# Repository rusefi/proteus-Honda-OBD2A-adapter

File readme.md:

https://github.com/rusefi/rusefi and https://github.com/mck1117/proteus

https://github.com/rusefi/rusefi/wiki/Vault-Of-Honda-OEM#obd-2

https://github.com/rusefi/rusefi/wiki/Honda-Civic-1996

https://github.com/rusefi/rusefi/wiki/Honda-Accord-1995

[Connector spreadsheet](https://docs.google.com/spreadsheets/d/1NOu2Atvwz7war0sTAcp2MZZhsYdLY6VmwkuC-S1-yEU)

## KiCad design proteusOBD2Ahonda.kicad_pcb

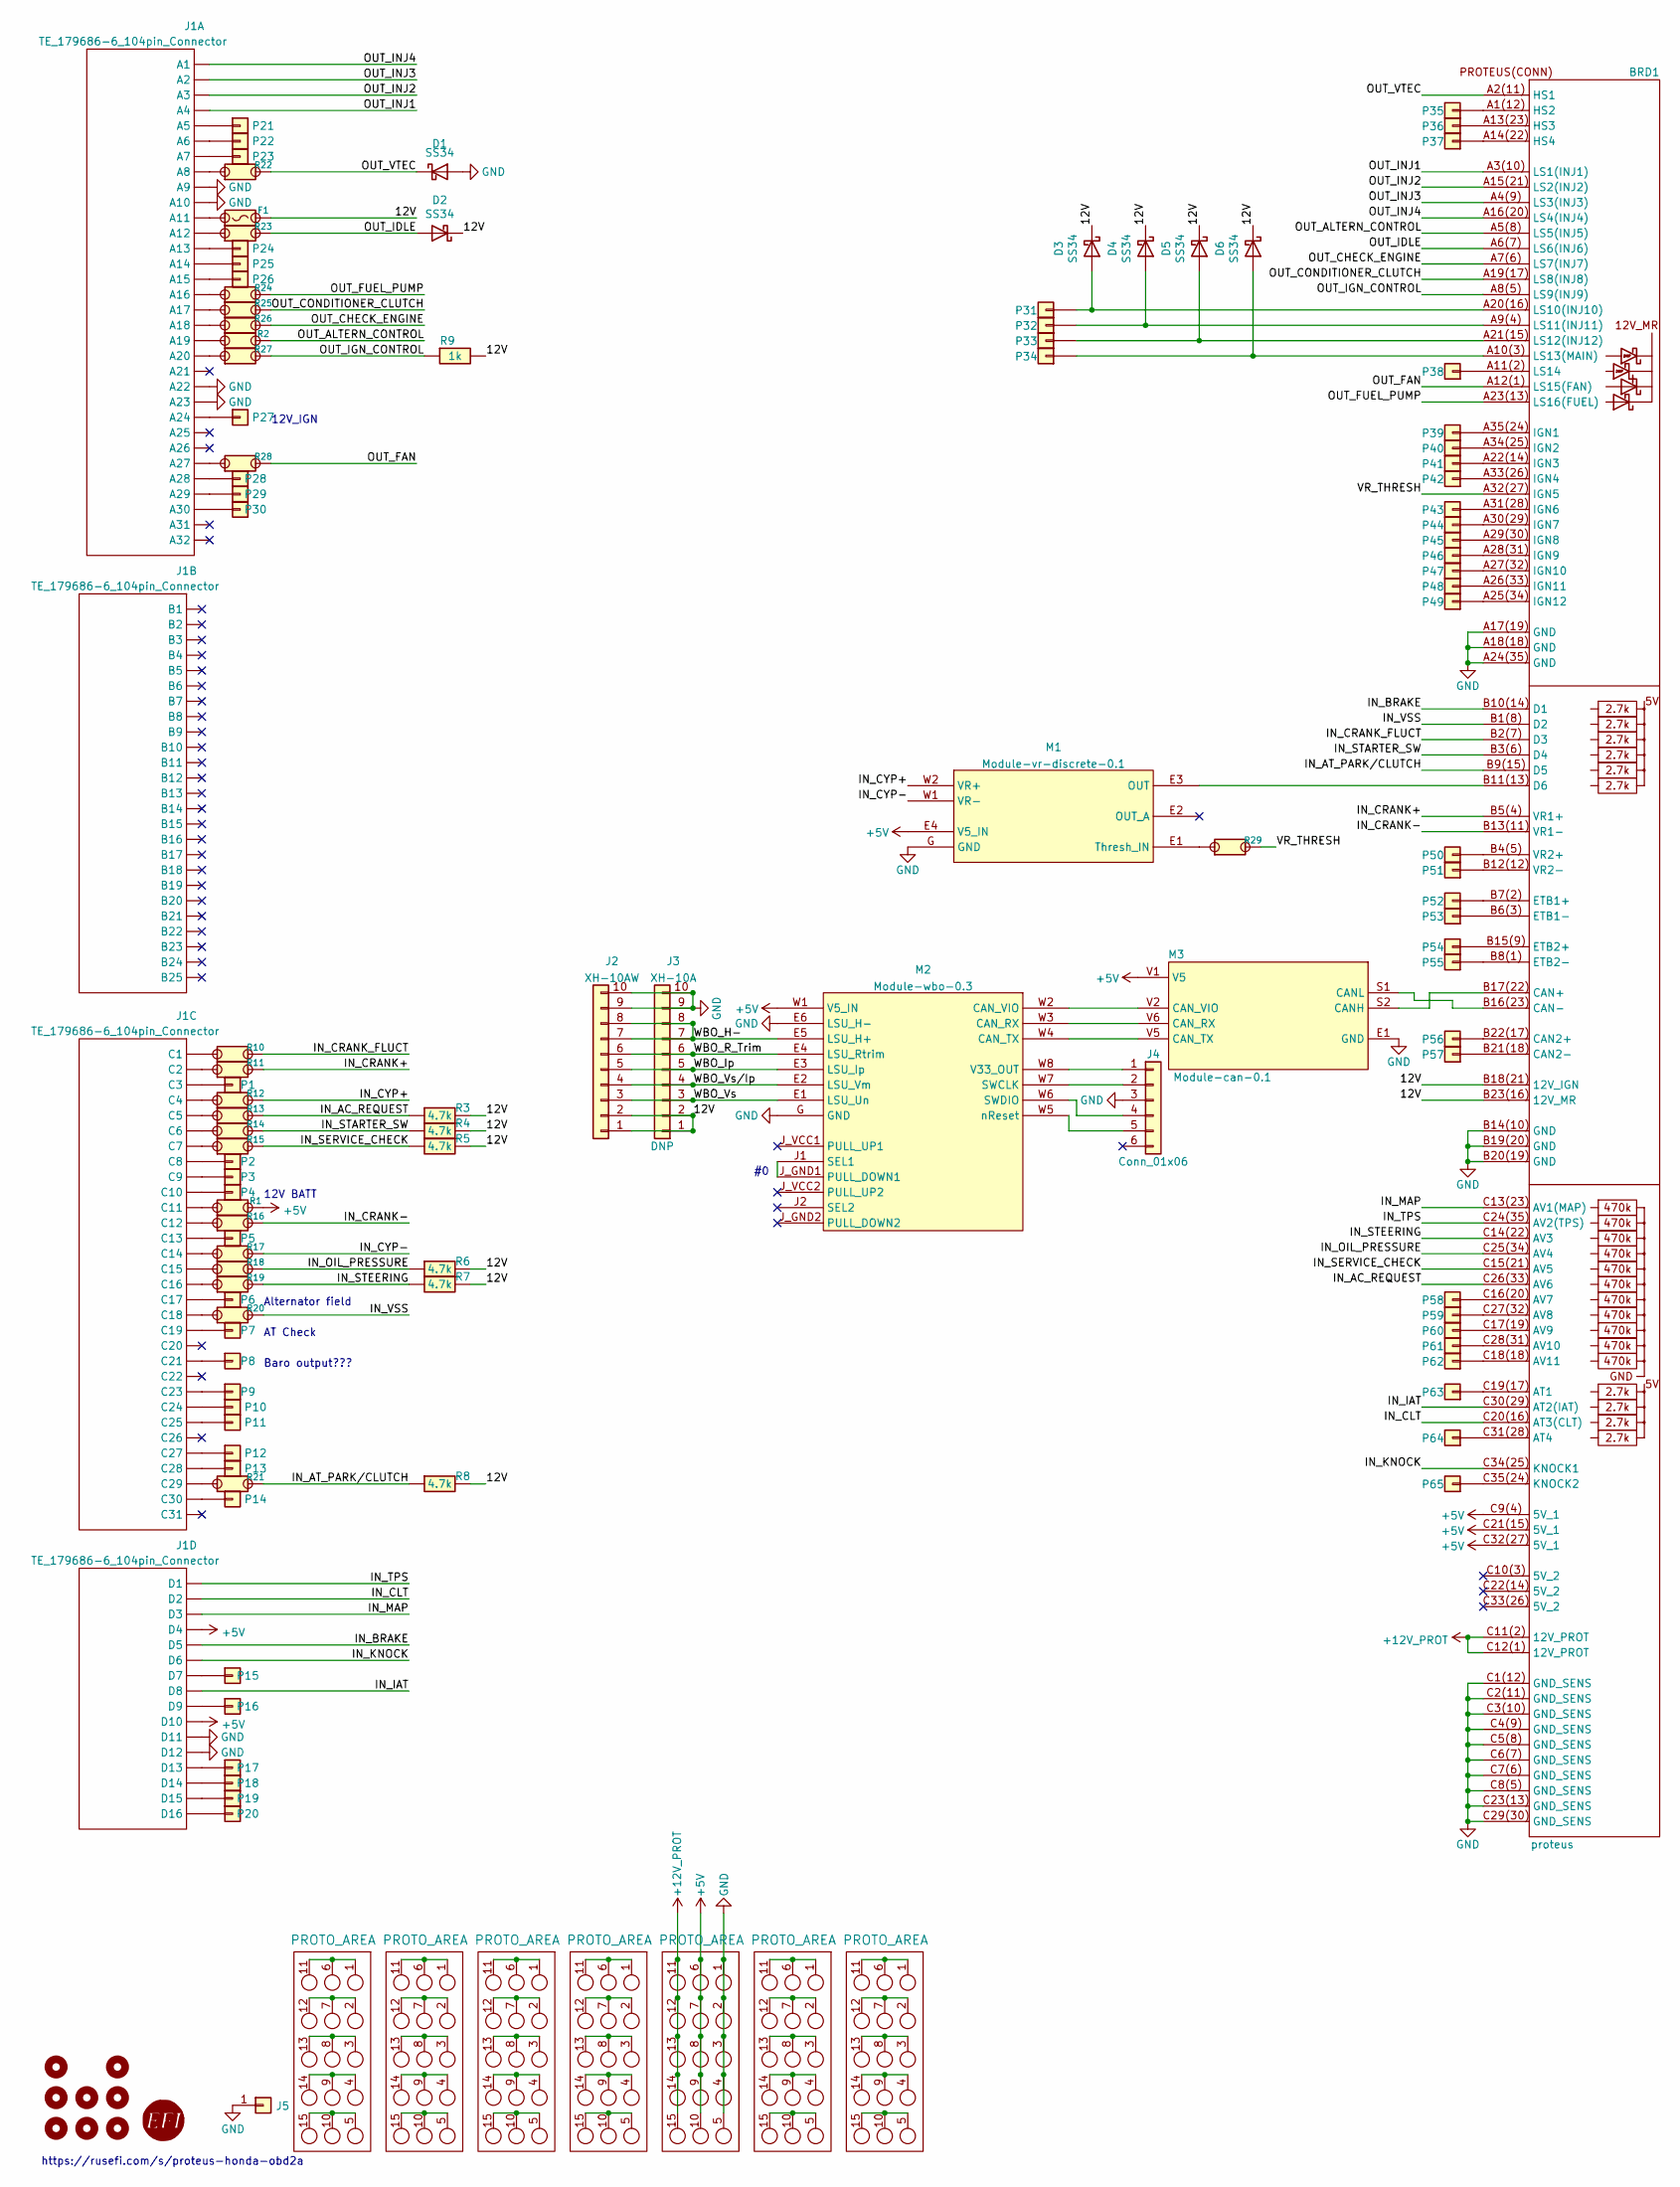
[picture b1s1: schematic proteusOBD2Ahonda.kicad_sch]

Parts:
BRD1: proteus
D1, D2, D3, D4, D5, D6: SS34; D_SMA; LCSC C8678
F1: Fuse-Pad-Pad; PAD-1206-PAD; LCSC C182446
G1: RUSEFI_LOGO; rusefi_logo
G2, G3, G4, G5, G6, G7, G8: PROTO_AREA
H1, H2, H3, H4, H5, H6, H7, H8: MountingHole; MountingHole_4.3mm_M4
J1: TE_179686-6_104pin_Connector
J2: XH-10AW; JST_XH_S10B-XH-A_1x10_P2.50mm_Horizontal; LCSC C14652
J3: XH-10A; JST_XH_B10B-XH-A_1x10_P2.50mm_Vertical; LCSC C8885
J4: Conn_01x06; PinHeader_1x06_P2.54mm_Vertical
J5: Conn_01x01; TestPoint_Pad_D2.0mm
M1: Module-vr-discrete-0.1; vr-discrete
M2: Module-wbo-0.3; wbo
M3: Module-can-0.1; can
P1, P2, P3, P4, P5, P6, P7, P8, P9, P10, P11, P12, P13, P14, P15, P16, P17, P18, P19, P20, P21, P22, P23, P24, P25, P26, P27, P28, P29, P30, P31, P32, P33, P34, P35, P36, P37, P38, P39, P40, P41, P42, P43, P44, P45, P46, P47, P48, P49, P50, P51, P52, P53, P54, P55, P56, P57, P58, P59, P60, P61, P62, P63, P64, P65: Pad; PAD-TH
R1, R2, R10, R11, R12, R13, R14, R15, R16, R17, R18, R19, R20, R21, R22, R23, R24, R25, R26, R27, R28, R29: Jumper-Pad-Pad; PAD-0805-PAD; LCSC C17477
R3, R4, R5, R6, R7, R8: 4.7k; R0603; LCSC C23162
R9: 1k; R1206; LCSC C4410

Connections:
+5V: BRD1.C9(4) (5V_1), BRD1.C21(15) (5V_1), BRD1.C32(27) (5V_1), G6.6, G6.7, G6.8, G6.9, G6.10, J1.D4, J1.D10, M1.E4 (V5_IN), M2.W1 (V5_IN), M3.V1 (V5), R1.2
+12V_PROT: BRD1.C11(2) (12V_PROT), BRD1.C12(1) (12V_PROT), G6.11, G6.12, G6.13, G6.14, G6.15
/12V: BRD1.B18(21) (12V_IGN), BRD1.B23(16) (12V_MR), D2.1 (K), D3.1 (K), D4.1 (K), D5.1 (K), D6.1 (K), F1.2, J2.1, J2.2, J3.1, J3.2, R3.2, R4.2, R5.2, R6.2, R7.2, R8.2, R9.2
/IN_AC_REQUEST: BRD1.C26(33) (AV6), R3.1, R13.2
/IN_AT_PARK/CLUTCH: BRD1.B9(15) (D5), R8.1, R21.2
/IN_BRAKE: BRD1.B10(14) (D1), J1.D5
/IN_CLT: BRD1.C20(16) (AT3(CLT)), J1.D2
/IN_CRANK+: BRD1.B5(4) (VR1+), R11.2
/IN_CRANK-: BRD1.B13(11) (VR1-), R16.2
/IN_CRANK_FLUCT: BRD1.B2(7) (D3), R10.2
/IN_CYP+: M1.W2 (VR+), R12.2
/IN_CYP-: M1.W1 (VR-), R17.2
/IN_IAT: BRD1.C30(29) (AT2(IAT)), J1.D8
/IN_KNOCK: BRD1.C34(25) (KNOCK1), J1.D6
/IN_MAP: BRD1.C13(23) (AV1(MAP)), J1.D3
/IN_OIL_PRESSURE: BRD1.C25(34) (AV4), R6.1, R18.2
/IN_SERVICE_CHECK: BRD1.C15(21) (AV5), R5.1, R15.2
/IN_STARTER_SW: BRD1.B3(6) (D4), R4.1, R14.2
/IN_STEERING: BRD1.C14(22) (AV3), R7.1, R19.2
/IN_TPS: BRD1.C24(35) (AV2(TPS)), J1.D1
/IN_VSS: BRD1.B1(8) (D2), R20.2
/OUT_ALTERN_CONTROL: BRD1.A5(8) (LS5(INJ5)), R2.2
/OUT_CHECK_ENGINE: BRD1.A7(6) (LS7(INJ7)), R26.2
/OUT_CONDITIONER_CLUTCH: BRD1.A19(17) (LS8(INJ8)), R25.2
/OUT_FAN: BRD1.A12(1) (LS15(FAN)), R28.2
/OUT_FUEL_PUMP: BRD1.A23(13) (LS16(FUEL)), R24.2
/OUT_IDLE: BRD1.A6(7) (LS6(INJ6)), D2.2 (A), R23.2
/OUT_IGN_CONTROL: BRD1.A8(5) (LS9(INJ9)), R9.1, R27.2
/OUT_INJ1: BRD1.A3(10) (LS1(INJ1)), J1.A4
/OUT_INJ2: BRD1.A15(21) (LS2(INJ2)), J1.A3
/OUT_INJ3: BRD1.A4(9) (LS3(INJ3)), J1.A2
/OUT_INJ4: BRD1.A16(20) (LS4(INJ4)), J1.A1
/OUT_VTEC: BRD1.A2(11) (HS1), D1.1 (K), R22.2
/VR_THRESH: BRD1.A32(27) (IGN5), R29.2
/WBO_H-: J2.7, J2.8, J3.7, J3.8, M2.E5 (LSU_H+)
/WBO_Ip: J2.5, J3.5, M2.E3 (LSU_Ip)
/WBO_R_Trim: J2.6, J3.6, M2.E4 (LSU_Rtrim)
/WBO_Vs: J2.3, J3.3, M2.E1 (LSU_Un)
/WBO_Vs/Ip: J2.4, J3.4, M2.E2 (LSU_Vm)
GND: BRD1.A17(19) (GND), BRD1.A18(18) (GND), BRD1.A24(35) (GND), BRD1.B14(10) (GND), BRD1.B19(20) (GND), BRD1.B20(19) (GND), BRD1.C1(12) (GND_SENS), BRD1.C2(11) (GND_SENS), BRD1.C3(10) (GND_SENS), BRD1.C4(9) (GND_SENS), BRD1.C5(8) (GND_SENS), BRD1.C6(7) (GND_SENS), BRD1.C7(6) (GND_SENS), BRD1.C8(5) (GND_SENS), BRD1.C23(13) (GND_SENS), BRD1.C29(30) (GND_SENS), D1.2 (A), G6.1, G6.2, G6.3, G6.4, G6.5, J1.A9, J1.A10, J1.A22, J1.A23, J1.D11, J1.D12, J2.9, J2.10, J3.9, J3.10, J4.3, J5.1, M1.G (GND), M2.E6 (LSU_H-), M2.G (GND), M3.E1 (GND)
unnamed: BRD1.A1(12) (HS2), P35.1
unnamed: BRD1.A9(4) (LS11(INJ11)), D4.2 (A), P32.1
unnamed: BRD1.A10(3) (LS13(MAIN)), D6.2 (A), P34.1
unnamed: BRD1.A11(2) (LS14), P38.1
unnamed: BRD1.A13(23) (HS3), P36.1
unnamed: BRD1.A14(22) (HS4), P37.1
unnamed: BRD1.A20(16) (LS10(INJ10)), D3.2 (A), P31.1
unnamed: BRD1.A21(15) (LS12(INJ12)), D5.2 (A), P33.1
unnamed: BRD1.A22(14) (IGN3), P41.1
unnamed: BRD1.A25(34) (IGN12), P49.1
unnamed: BRD1.A26(33) (IGN11), P48.1
unnamed: BRD1.A27(32) (IGN10), P47.1
unnamed: BRD1.A28(31) (IGN9), P46.1
unnamed: BRD1.A29(30) (IGN8), P45.1
unnamed: BRD1.A30(29) (IGN7), P44.1
unnamed: BRD1.A31(28) (IGN6), P43.1
unnamed: BRD1.A33(26) (IGN4), P42.1
unnamed: BRD1.A34(25) (IGN2), P40.1
unnamed: BRD1.A35(24) (IGN1), P39.1
unnamed: BRD1.B4(5) (VR2+), P50.1
unnamed: BRD1.B6(3) (ETB1-), P53.1
unnamed: BRD1.B7(2) (ETB1+), P52.1
unnamed: BRD1.B8(1) (ETB2-), P55.1
unnamed: BRD1.B11(13) (D6), M1.E3 (OUT)
unnamed: BRD1.B12(12) (VR2-), P51.1
unnamed: BRD1.B15(9) (ETB2+), P54.1
unnamed: BRD1.B16(23) (CAN-), M3.S1 (CANL)
unnamed: BRD1.B17(22) (CAN+), M3.S2 (CANH)
unnamed: BRD1.B21(18) (CAN2-), P57.1
unnamed: BRD1.B22(17) (CAN2+), P56.1
unnamed: BRD1.C16(20) (AV7), P58.1
unnamed: BRD1.C17(19) (AV9), P60.1
unnamed: BRD1.C18(18) (AV11), P62.1
unnamed: BRD1.C19(17) (AT1), P63.1
unnamed: BRD1.C27(32) (AV8), P59.1
unnamed: BRD1.C28(31) (AV10), P61.1
unnamed: BRD1.C31(28) (AT4), P64.1
unnamed: BRD1.C35(24) (KNOCK2), P65.1
unnamed: F1.1, J1.A11
unnamed: G2.1, G2.6, G2.11
unnamed: G2.5, G2.10, G2.15
unnamed: G2.2, G2.7, G2.12
unnamed: G2.3, G2.8, G2.13
unnamed: G2.4, G2.9, G2.14
unnamed: G3.1, G3.6, G3.11
unnamed: G3.5, G3.10, G3.15
unnamed: G3.2, G3.7, G3.12
unnamed: G3.3, G3.8, G3.13
unnamed: G3.4, G3.9, G3.14
unnamed: G4.1, G4.6, G4.11
unnamed: G4.5, G4.10, G4.15
unnamed: G4.2, G4.7, G4.12
unnamed: G4.3, G4.8, G4.13
unnamed: G4.4, G4.9, G4.14
unnamed: G5.1, G5.6, G5.11
unnamed: G5.5, G5.10, G5.15
unnamed: G5.2, G5.7, G5.12
unnamed: G5.3, G5.8, G5.13
unnamed: G5.4, G5.9, G5.14
unnamed: G7.1, G7.6, G7.11
unnamed: G7.5, G7.10, G7.15
unnamed: G7.2, G7.7, G7.12
unnamed: G7.3, G7.8, G7.13
unnamed: G7.4, G7.9, G7.14
unnamed: G8.1, G8.6, G8.11
unnamed: G8.5, G8.10, G8.15
unnamed: G8.2, G8.7, G8.12
unnamed: G8.3, G8.8, G8.13
unnamed: G8.4, G8.9, G8.14
unnamed: J1.A5, P21.1
unnamed: J1.A6, P22.1
unnamed: J1.A7, P23.1
unnamed: J1.A8, R22.1
unnamed: J1.A12, R23.1
unnamed: J1.A13, P24.1
unnamed: J1.A14, P25.1
unnamed: J1.A15, P26.1
unnamed: J1.A16, R24.1
unnamed: J1.A17, R25.1
unnamed: J1.A18, R26.1
unnamed: J1.A19, R2.1
unnamed: J1.A20, R27.1
unnamed: J1.A24, P27.1
unnamed: J1.A27, R28.1
unnamed: J1.A28, P28.1
unnamed: J1.A29, P29.1
unnamed: J1.A30, P30.1
unnamed: J1.C1, R10.1
unnamed: J1.C2, R11.1
unnamed: J1.C3, P1.1
unnamed: J1.C4, R12.1
unnamed: J1.C5, R13.1
unnamed: J1.C6, R14.1
unnamed: J1.C7, R15.1
unnamed: J1.C8, P2.1
unnamed: J1.C9, P3.1
unnamed: J1.C10, P4.1
unnamed: J1.C11, R1.1
unnamed: J1.C12, R16.1
unnamed: J1.C13, P5.1
unnamed: J1.C14, R17.1
unnamed: J1.C15, R18.1
unnamed: J1.C16, R19.1
unnamed: J1.C17, P6.1
unnamed: J1.C18, R20.1
unnamed: J1.C19, P7.1
unnamed: J1.C21, P8.1
unnamed: J1.C23, P9.1
unnamed: J1.C24, P10.1
unnamed: J1.C25, P11.1
unnamed: J1.C27, P12.1
unnamed: J1.C28, P13.1
unnamed: J1.C29, R21.1
unnamed: J1.C30, P14.1
unnamed: J1.D7, P15.1
unnamed: J1.D9, P16.1
unnamed: J1.D13, P17.1
unnamed: J1.D14, P18.1
unnamed: J1.D15, P19.1
unnamed: J1.D16, P20.1
unnamed: J4.1, M2.W8 (V33_OUT)
unnamed: J4.2, M2.W7 (SWCLK)
unnamed: J4.4, M2.W6 (SWDIO)
unnamed: J4.5, M2.W5 (nReset)
unnamed: M1.E1 (Thresh_IN), R29.1
unnamed: M2.J1 (SEL1), M2.J_GND1 (PULL_DOWN1)
unnamed: M2.W2 (CAN_VIO), M3.V2 (CAN_VIO)
unnamed: M2.W3 (CAN_RX), M3.V6 (CAN_RX)
unnamed: M2.W4 (CAN_TX), M3.V5 (CAN_TX)

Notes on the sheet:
Alternator field
Baro output???
12V_IGN
https://rusefi.com/s/proteus-honda-obd2a
12V BATT
AT Check

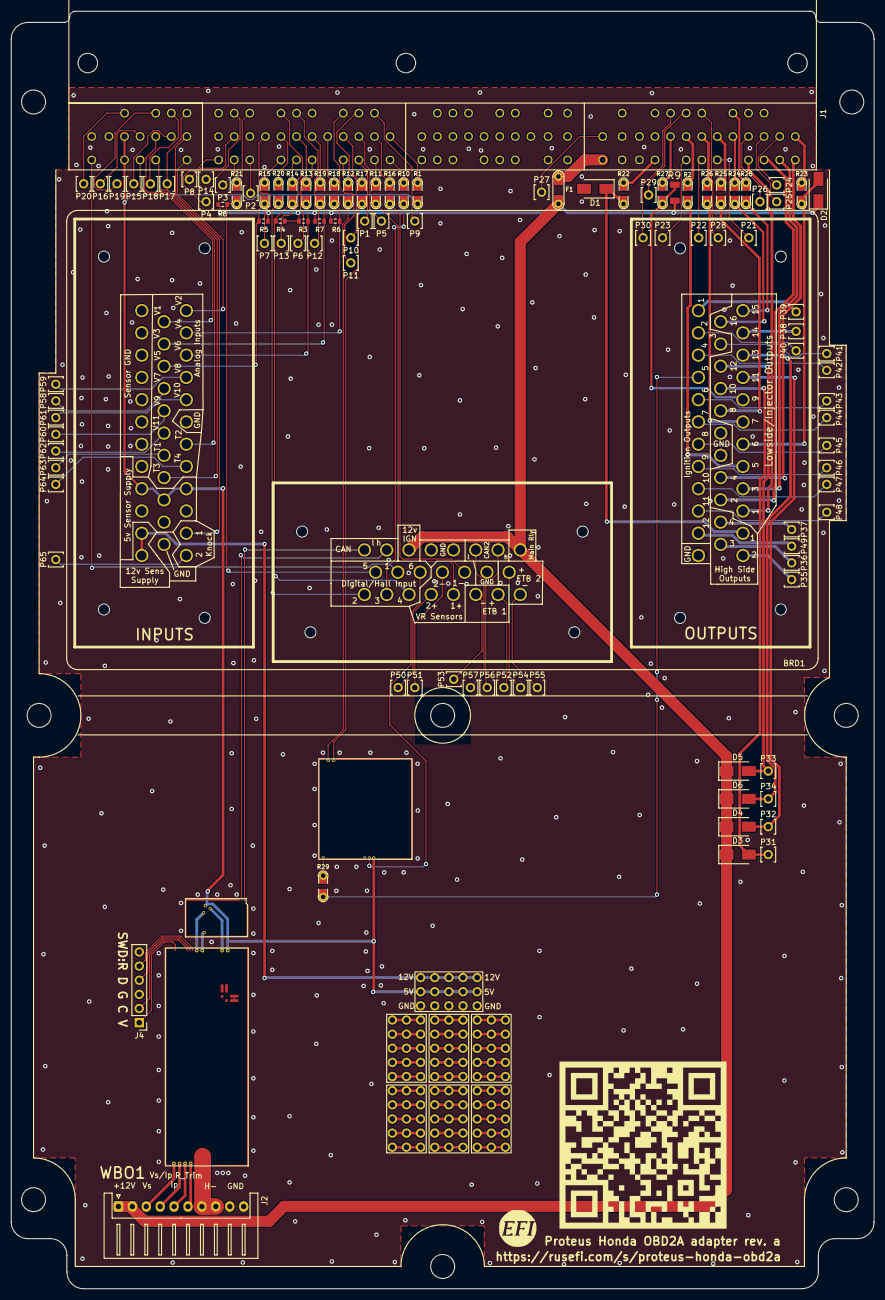
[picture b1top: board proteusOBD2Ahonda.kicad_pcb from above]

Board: 2 copper layers, 155.0 x 229.5 mm, 125 parts (1 on the bottom side), 169 nets.

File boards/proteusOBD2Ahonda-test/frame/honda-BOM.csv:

Comment,Designator,Footprint,LCSC Part #
"proteus","BRD1","proteus",""
"SS34","D1","D_SMA","C8678"
"SS34","D2","D_SMA","C8678"
"SS34","D3","D_SMA","C8678"
"SS34","D4","D_SMA","C8678"
"SS34","D5","D_SMA","C8678"
"SS34","D6","D_SMA","C8678"
"Fuse-Pad-Pad","F1","PAD-1206-PAD","C182446"
"RUSEFI_LOGO","G1","rusefi_logo",""
"PROTO_AREA","G2","PROTO_AREA",""
"PROTO_AREA","G3","PROTO_AREA",""
"PROTO_AREA","G4","PROTO_AREA",""
"PROTO_AREA","G5","PROTO_AREA",""
"PROTO_AREA","G6","PROTO_AREA",""
"PROTO_AREA","G7","PROTO_AREA",""
"PROTO_AREA","G8","PROTO_AREA",""
"MountingHole","H1","MountingHole_4.3mm_M4",""
"MountingHole","H2","MountingHole_4.3mm_M4",""
"MountingHole","H3","MountingHole_4.3mm_M4",""
"MountingHole","H4","MountingHole_4.3mm_M4",""
"MountingHole","H5","MountingHole_4.3mm_M4",""
"MountingHole","H6","MountingHole_4.3mm_M4",""
"MountingHole","H7","MountingHole_4.3mm_M4",""
"MountingHole","H8","MountingHole_4.3mm_M4",""
"TE_179686-6_104pin_Connector","J1","TE_179686-6_104pin_Connector",""
"XH-10AW","J2","JST_XH_S10B-XH-A_1x10_P2.50mm_Horizontal","C14652"
"XH-10A","J3","JST_XH_B10B-XH-A_1x10_P2.50mm_Vertical",""
"Conn_01x06","J4","PinHeader_1x06_P2.54mm_Vertical",""
"Conn_01x01","J5","TestPoint_Pad_D2.0mm",""
"Module:vr-discrete/0.1","M1","vr-discrete",""
"Module:wbo/0.3","M2","wbo",""
"Module:can/0.1","M3","can",""
"Pad","P1","PAD-TH",""
"Pad","P2","PAD-TH",""
"Pad","P3","PAD-TH",""
"Pad","P4","PAD-TH",""
"Pad","P5","PAD-TH",""
"Pad","P6","PAD-TH",""
"Pad","P7","PAD-TH",""
"Pad","P8","PAD-TH",""
"Pad","P9","PAD-TH",""
"Pad","P10","PAD-TH",""
"Pad","P11","PAD-TH",""
"Pad","P12","PAD-TH",""
"Pad","P13","PAD-TH",""
"Pad","P14","PAD-TH",""
"Pad","P15","PAD-TH",""
"Pad","P16","PAD-TH",""
"Pad","P17","PAD-TH",""
"Pad","P18","PAD-TH",""
"Pad","P19","PAD-TH",""
"Pad","P20","PAD-TH",""
"Pad","P21","PAD-TH",""
"Pad","P22","PAD-TH",""
"Pad","P23","PAD-TH",""
"Pad","P24","PAD-TH",""
"Pad","P25","PAD-TH",""
"Pad","P26","PAD-TH",""
"Pad","P27","PAD-TH",""
"Pad","P28","PAD-TH",""
"Pad","P29","PAD-TH",""
"Pad","P30","PAD-TH",""
"Pad","P31","PAD-TH",""
"Pad","P32","PAD-TH",""
"Pad","P33","PAD-TH",""
"Pad","P34","PAD-TH",""
"Pad","P35","PAD-TH",""
"Pad","P36","PAD-TH",""
"Pad","P37","PAD-TH",""
"Pad","P38","PAD-TH",""
"Pad","P39","PAD-TH",""
"Pad","P40","PAD-TH",""
"Pad","P41","PAD-TH",""
"Pad","P42","PAD-TH",""
"Pad","P43","PAD-TH",""
"Pad","P44","PAD-TH",""
"Pad","P45","PAD-TH",""
"Pad","P46","PAD-TH",""
"Pad","P47","PAD-TH",""
"Pad","P48","PAD-TH",""
"Pad","P49","PAD-TH",""
"Pad","P50","PAD-TH",""
"Pad","P51","PAD-TH",""
"Pad","P52","PAD-TH",""
"Pad","P53","PAD-TH",""
"Pad","P54","PAD-TH",""
"Pad","P55","PAD-TH",""
"Pad","P56","PAD-TH",""
"Pad","P57","PAD-TH",""
"Pad","P58","PAD-TH",""
"Pad","P59","PAD-TH",""
"Pad","P60","PAD-TH",""
"Pad","P61","PAD-TH",""
"Pad","P62","PAD-TH",""
"Pad","P63","PAD-TH",""
"Pad","P64","PAD-TH",""
"Pad","P65","PAD-TH",""
"Jumper-Pad-Pad","R1","PAD-0805-PAD","C17477"
"Jumper-Pad-Pad","R2","PAD-0805-PAD","C17477"
"4.7k","R3","R0603","C23162"
"4.7k","R4","R0603","C23162"
"4.7k","R5","R0603","C23162"
"4.7k","R6","R0603","C23162"
"4.7k","R7","R0603","C23162"
"4.7k","R8","R0603","C23162"
"1k","R9","R1206","C4410"
"Jumper-Pad-Pad","R10","PAD-0805-PAD","C17477"
"Jumper-Pad-Pad","R11","PAD-0805-PAD","C17477"
"Jumper-Pad-Pad","R12","PAD-0805-PAD","C17477"
"Jumper-Pad-Pad","R13","PAD-0805-PAD","C17477"
"Jumper-Pad-Pad","R14","PAD-0805-PAD","C17477"
"Jumper-Pad-Pad","R15","PAD-0805-PAD","C17477"
"Jumper-Pad-Pad","R16","PAD-0805-PAD","C17477"
"Jumper-Pad-Pad","R17","PAD-0805-PAD","C17477"
"Jumper-Pad-Pad","R18","PAD-0805-PAD","C17477"
"Jumper-Pad-Pad","R19","PAD-0805-PAD","C17477"
"Jumper-Pad-Pad","R20","PAD-0805-PAD","C17477"
"Jumper-Pad-Pad","R21","PAD-0805-PAD","C17477"
"Jumper-Pad-Pad","R22","PAD-0805-PAD","C17477"
"Jumper-Pad-Pad","R23","PAD-0805-PAD","C17477"
"Jumper-Pad-Pad","R24","PAD-0805-PAD","C17477"
"Jumper-Pad-Pad","R25","PAD-0805-PAD","C17477"
"Jumper-Pad-Pad","R26","PAD-0805-PAD","C17477"
"Jumper-Pad-Pad","R27","PAD-0805-PAD","C17477"
"Jumper-Pad-Pad","R28","PAD-0805-PAD","C17477"
"Jumper-Pad-Pad","R29","PAD-0805-PAD","C17477"

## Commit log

2021-09-29 104 kicad component
2021-10-01 Connector and proteus
2021-10-26 Outline
2021-10-27 Upd pinout
2021-10-30 Upd sch, pcb
2021-10-31 Upd pcb
2021-11-04 Fab preview
2024-01-12 fresh hellen
2024-01-12 some dead files
2024-01-12 progress
2024-01-12 2024 process
2024-01-12 [skip actions] Auto-generated board v2.1
2024-01-12 just mimicking 2024 convention
